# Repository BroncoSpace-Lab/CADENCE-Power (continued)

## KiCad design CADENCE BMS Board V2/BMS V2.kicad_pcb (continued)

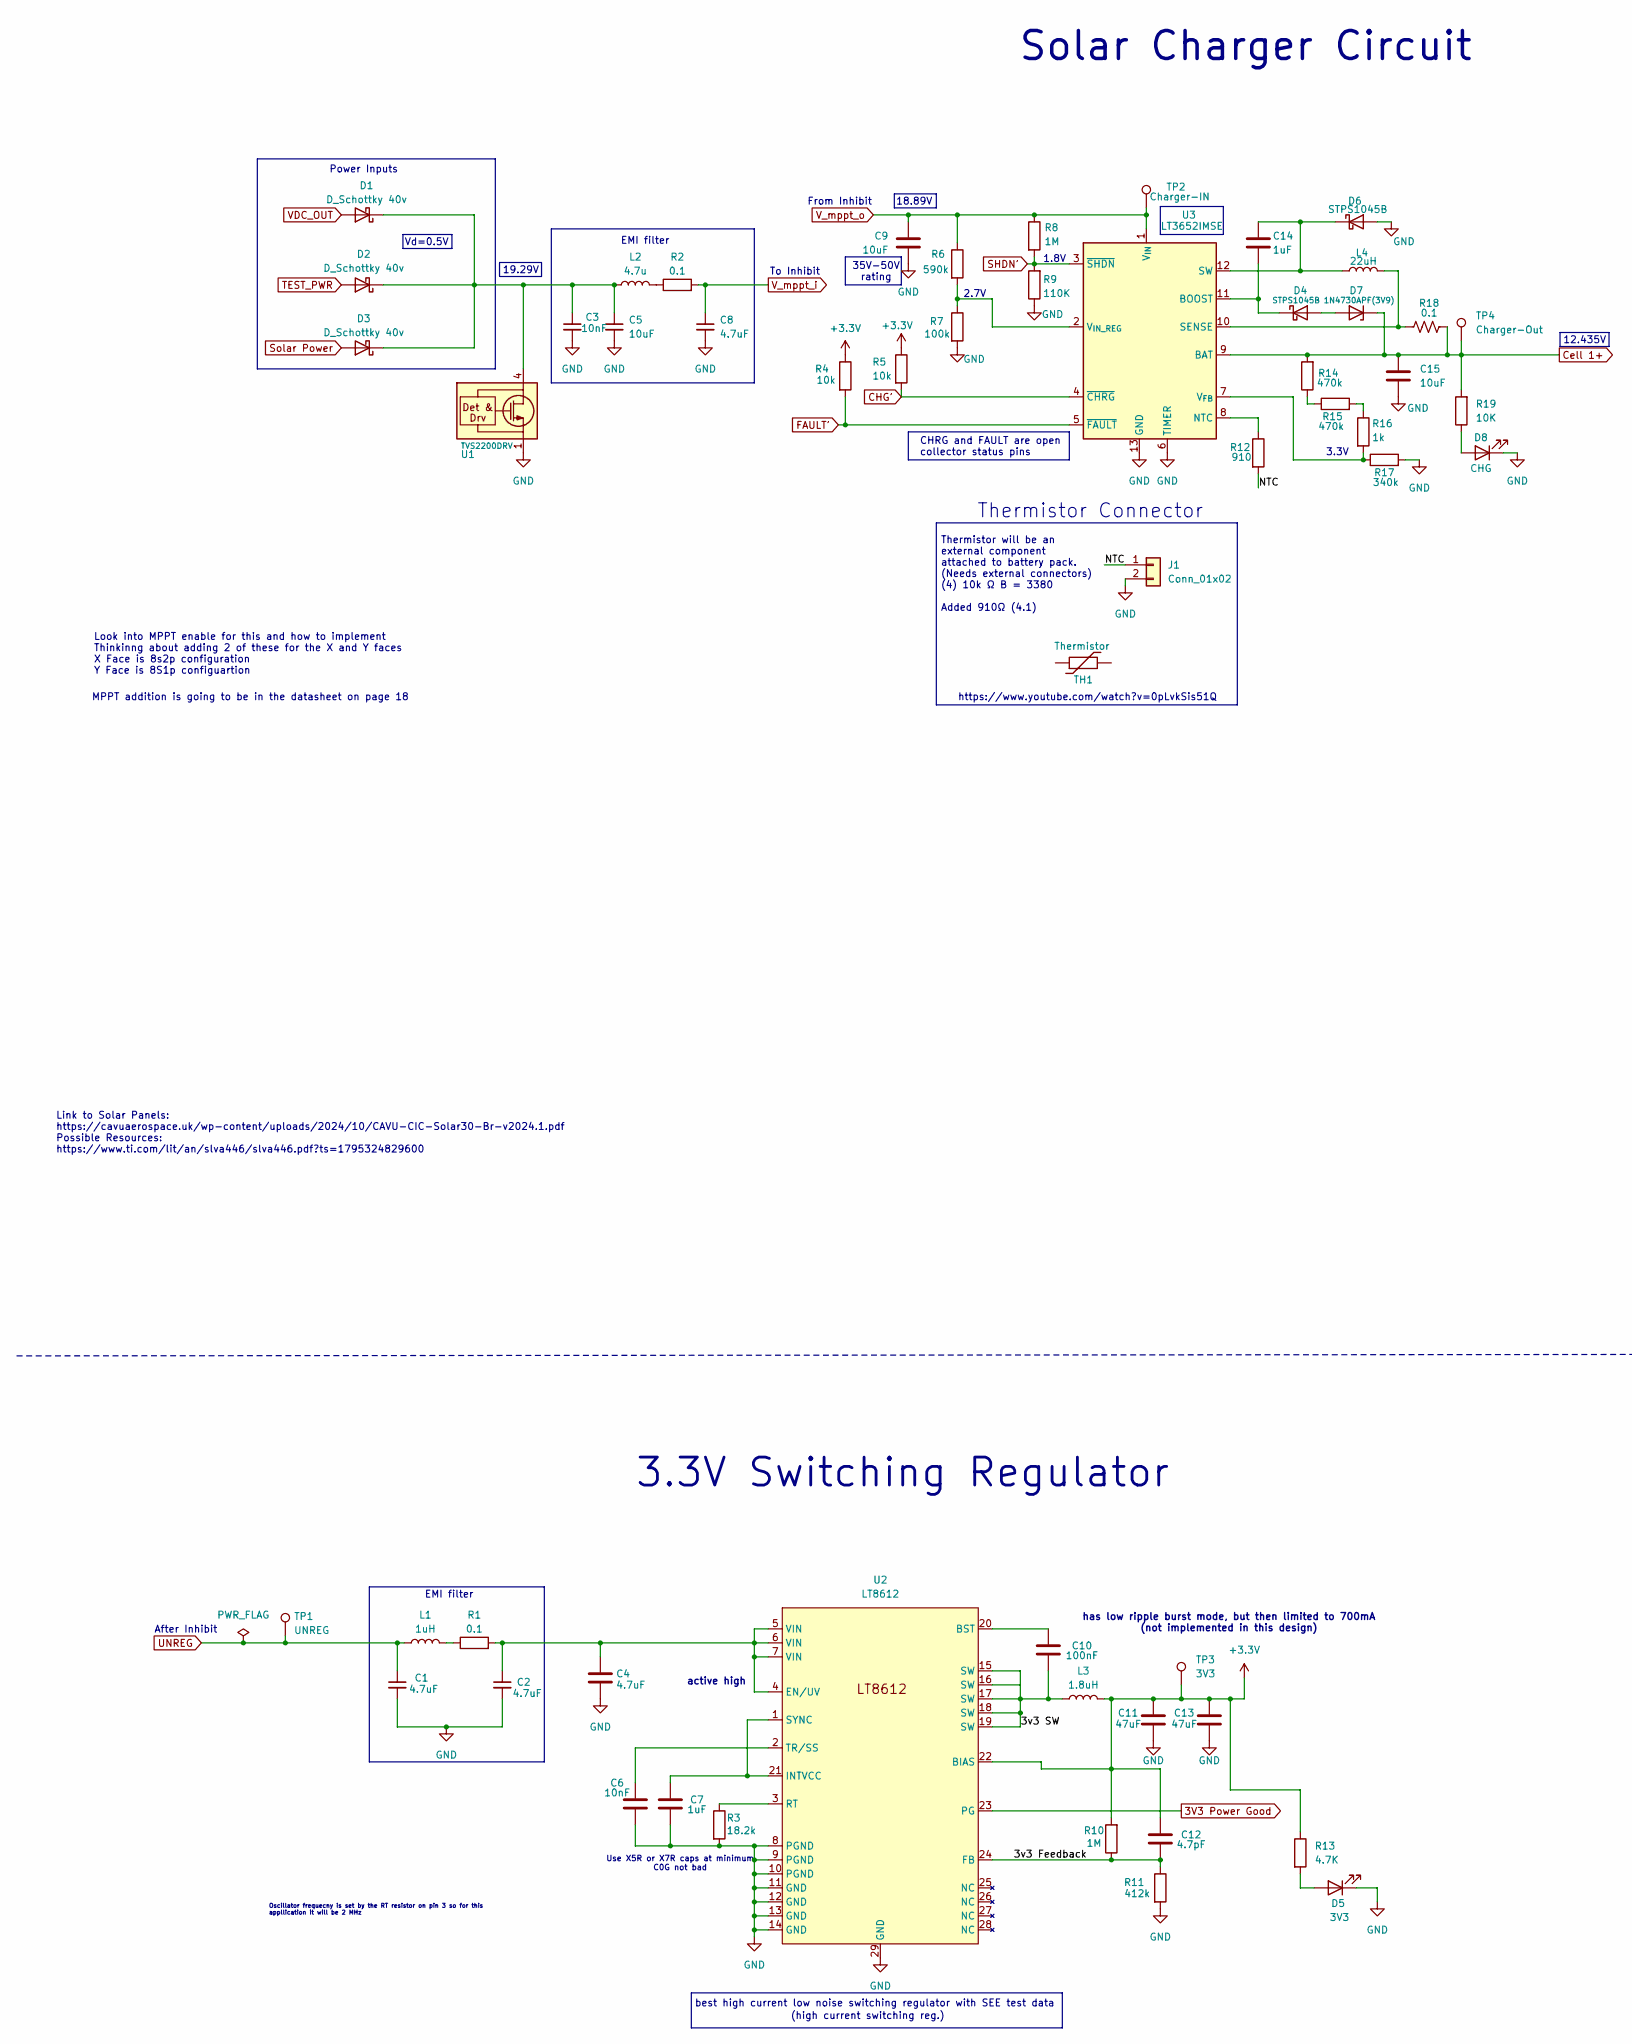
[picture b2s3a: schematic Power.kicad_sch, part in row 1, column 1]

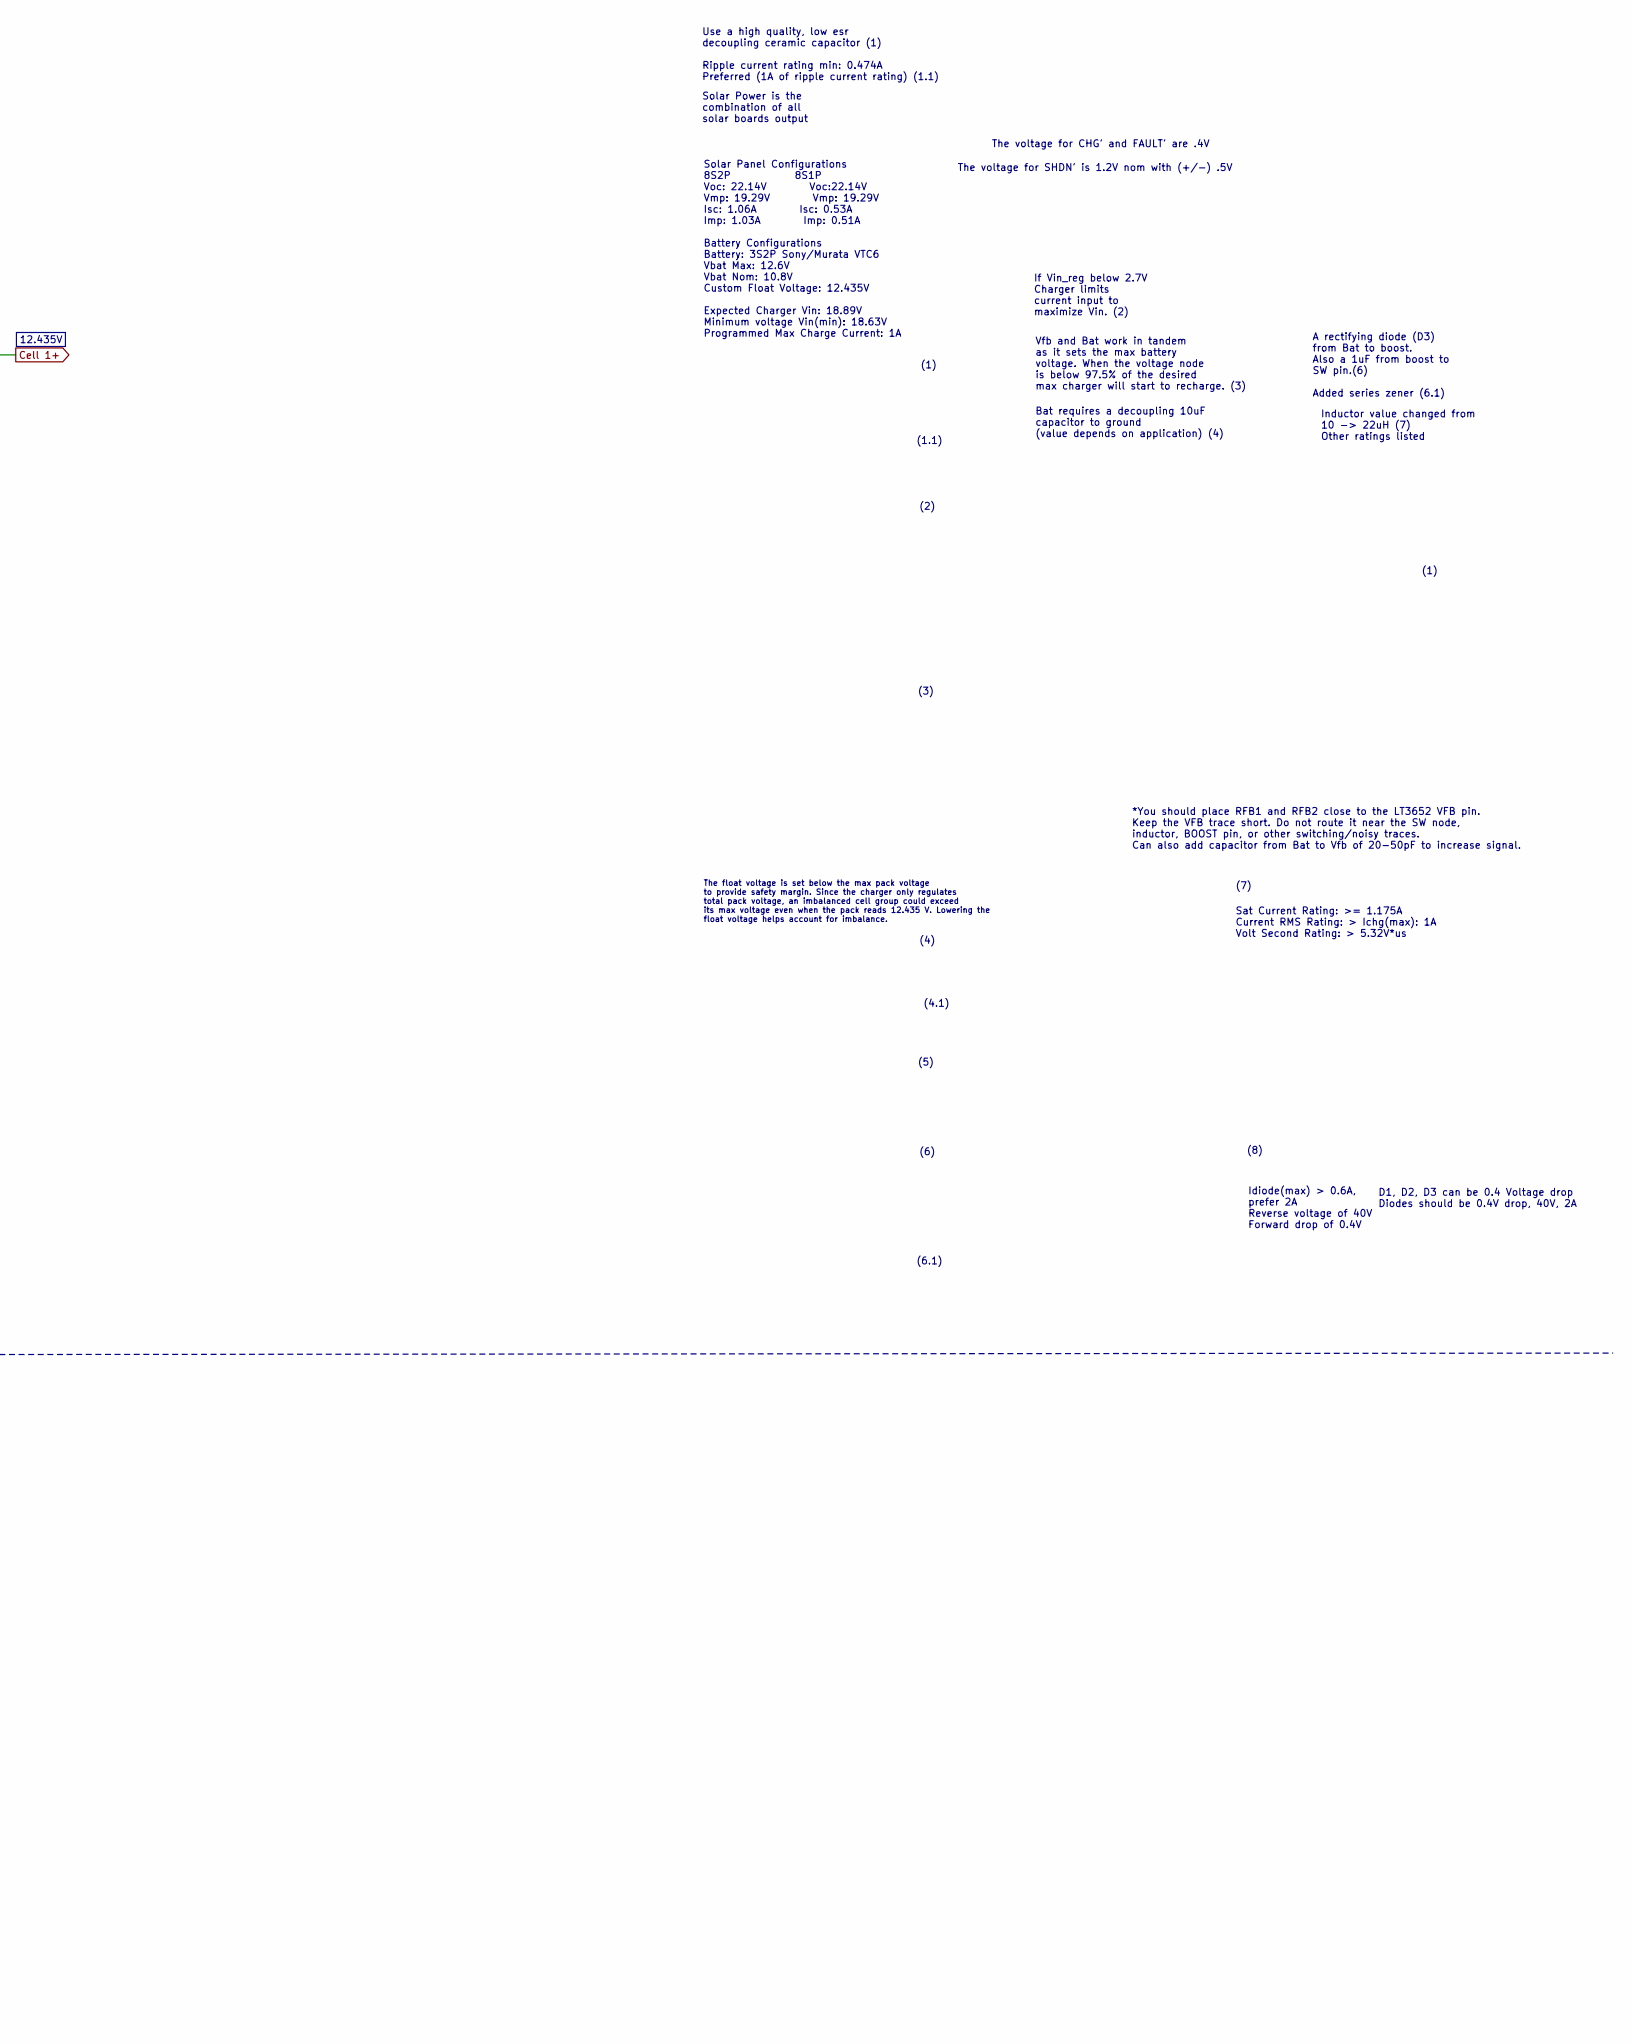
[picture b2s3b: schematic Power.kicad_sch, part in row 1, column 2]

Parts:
C1, C2, C4, C8: 4.7uF; C_1206_3216Metric
C3, C6: 10nF; C_0805_2012Metric
C5, C9, C15: 10uF; C_1210_3225Metric
C7, C14: 1uF; C_0805_2012Metric
C10: 100nF; C_0402_1005Metric
C11, C13: 47uF; C_2220_5750Metric
C12: 4.7pF; C_0603_1608Metric
D1, D2, D3: D_Schottky 40v; D_SMA
D4, D6: STPS1045B; DPAK_STM
D5: 3V3; LED_0402_1005Metric
D7: 1N4730APF(3V9); D_DO-41_SOD81_P12.70mm_Horizontal
D8: CHG; LED_0402_1005Metric
J1: Conn_01x02; JST_GH_SM02B-GHS-TB_1x02-1MP_P1.25mm_Horizontal
L1: 1uH; L_Taiyo-Yuden_NR-40xx
L2: 4.7u; FNR5040S4R7MT
L3: 1.8uH; L_Taiyo-Yuden_NR-40xx
L4: 22uH; L_10.4x10.4_H4.8
R1: 0.1; R_1206_3216Metric
R2, R18: 0.1; R_2512_6332Metric
R3: 18.2k; R_0603_1608Metric
R4, R5: 10k; R_1210_3225Metric
R6: 590k; R_0402_1005Metric_Pad0.72x0.64mm_HandSolder
R7: 100k; R_1206_3216Metric
R8: 1M
R9: 110K
R10: 1M; R_2512_6332Metric
R11: 412k; R_1206_3216Metric
R12: 910; R_0603_1608Metric
R13: 4.7K; R_1206_3216Metric
R14, R15: 470k; R_0603_1608Metric
R16: 1k; R_0603_1608Metric
R17: 340k; R_1206_3216Metric
R19: 10K; R_1210_3225Metric
TH1: Thermistor
TP1: UNREG; TestPoint_THTPad_D1.0mm_Drill0.5mm
TP2: Charger-IN; TestPoint_THTPad_D1.0mm_Drill0.5mm
TP3: 3V3; TestPoint_THTPad_D1.0mm_Drill0.5mm
TP4: Charger-Out; TestPoint_THTPad_D1.0mm_Drill0.5mm
U1: TVS2200DRV; WSON-6-1EP_2x2mm_P0.65mm_EP1x1.6mm
U2: LT8612; QFN50P300X600X80-29N-D
U3: LT3652IMSE; MSOP-12-1EP_3x4.039mm_P0.65mm_EP1.651x2.845mm

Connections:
3V3 Power Good: U2.23 (PG); also elsewhere on the board
+3.3V: C11.2, C12.2, C13.2, L3.2, R4.1, R5.1, R10.2, R13.1, TP3.1 (1_1), U2.22 (BIAS); also elsewhere on the board
/Power/3v3 Feedback: C12.1, R10.1, R11.1, U2.24 (FB)
/Power/3v3 SW: C10.1, L3.1, U2.15 (SW), U2.16 (SW), U2.17 (SW), U2.18 (SW), U2.19 (SW)
/Power/NTC: J1.1, R12.2
CHG': R5.2, U3.4 (~CHRG); also elsewhere on the board
Cell 1+: C15.1, D7.1 (K), R14.2, R18.2, R19.2, TP4.1 (1_1), U3.9 (BAT); also elsewhere on the board
FAULT': R4.2, U3.5 (~FAULT); also elsewhere on the board
unnamed: C3.1, C5.1, D1.1 (K), D2.1 (K), D3.1 (K), L2.1, U1.4 (IN), U1.5 (IN), U1.6 (IN)
unnamed: D4.1 (A), D7.2 (A)
unnamed: C14.2, D4.2 (K), U3.11 (BOOST)
unnamed: D5.2 (A), R13.2
unnamed: C14.1, D6.2 (K), L4.1, U3.12 (SW)
unnamed: D8.2 (A), R19.1
unnamed: L1.2, R1.1
unnamed: L2.2, R2.1
unnamed: R14.1, R15.1
unnamed: R15.2, R16.1
unnamed: C10.2, U2.20 (BST)
unnamed: C2.1, C4.1, R1.2, U2.4 (EN/UV), U2.5 (VIN), U2.6 (VIN), U2.7 (VIN)
unnamed: C7.2, U2.1 (SYNC), U2.21 (INTVCC)
unnamed: R3.1, U2.3 (RT)
unnamed: C6.2, U2.2 (TR/SS)
unnamed: R12.1, U3.8 (NTC)
unnamed: L4.2, R18.1, U3.10 (SENSE)
unnamed: R16.2, R17.1, U3.7 (V_{FB})
unnamed: R6.2, R7.1, U3.2 (V_{IN_REG})
SHDN': R8.2, R9.2, U3.3 (~SHDN); also elsewhere on the board
Solar1-: C1.2, C2.2, C3.2, C4.2, C5.2, C6.1, C7.1, C8.2, C9.2, C11.1, C13.1, C15.2, D5.1 (K), D6.1 (A), D8.1 (K), J1.2, R3.2, R7.2, R9.1, R11.2, R17.2, U1.1 (GND), U1.2 (GND), U1.3 (GND), U1.7 (GND), U2.8 (PGND), U2.9 (PGND), U2.10 (PGND), U2.11 (GND), U2.12 (GND), U2.13 (GND), U2.14 (GND), U2.29 (GND), U3.6 (TIMER), U3.13 (GND); also elsewhere on the board
Solar Power: D3.2 (A); also elsewhere on the board
TEST_PWR: D2.2 (A)
UNREG: C1.1, L1.1, TP1.1 (1_1); also elsewhere on the board
VDC_OUT: D1.2 (A); also elsewhere on the board
V_mppt_i: C8.1, R2.2; also elsewhere on the board
V_mppt_o: C9.1, R6.1, R8.1, TP2.1 (1_1), U3.1 (V_{IN}); also elsewhere on the board

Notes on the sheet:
Use X5R or X7R caps at minimum C0G not bad
(4.1)
MPPT addition is going to be in the datasheet on page 18
*You should place RFB1 and RFB2 close to the LT3652 VFB pin. Keep the VFB trace short. Do not route it near the SW node, inductor, BOOST pin, or other switching/noisy traces. Can also add capacitor from Bat to Vfb of 20-50pF to increase signal.
Link to Solar Panels: https://cavuaerospace.uk/wp-content/uploads/2024/10/CAVU-CIC-Solar30-Br-v2024.1.pdf Possible Resources: https://www.ti.com/lit/an/slva446/slva446.pdf?ts=1795324829600
Idiode(max) > 0.6A, prefer 2A Reverse voltage of 40V Forward drop of 0.4V
Inductor value changed from 10 -> 22uH (7) Other ratings listed
(3)
https://www.youtube.com/watch?v=0pLvkSis51Q
EMI filter
The voltage for SHDN' is 1.2V nom with (+/-) .5V
(6)
The float voltage is set below the max pack voltage to provide safety margin. Since the charger only regulates total pack voltage, an imbalanced cell group could exceed its max voltage even when the pack reads 12.435 V. Lowering the float voltage helps account for imbalance.
(8)
Oscillator frequecny is set by the RT resistor on pin 3 so for this appllication it will be 2 MHz
(1)
has low ripple burst mode, but then limited to 700mA (not implemented in this design)
best high current low noise switching regulator with SEE test data
From Inhibit
After Inhibit
If Vin_reg below 2.7V Charger limits current input to maximize Vin. (2)
D1, D2, D3 can be 0.4 Voltage drop Diodes should be 0.4V drop, 40V, 2A
(4)
Power Inputs
Solar Power is the combination of all solar boards output
1.8V
19.29V
Solar Panel Configurations 8S2P 8S1P Voc: 22.14V Voc:22.14V Vmp: 19.29V Vmp: 19.29V Isc: 1.06A Isc: 0.53A Imp: 1.03A Imp: 0.51A Battery Configurations Battery: 3S2P Sony/Murata VTC6 Vbat Max: 12.6V Vbat Nom: 10.8V Custom Float Voltage: 12.435V Expected Charger Vin: 18.89V Minimum voltage Vin(min): 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
3.3V Switching Regulator
The voltage for CHG' and FAULT' are .4V
To Inhibit
(5)
18.89V
Vd=0.5V
35V-50V rating
Sat Current Rating: >= 1.175A Current RMS Rating: > Ichg(max): 1A Volt Second Rating: > 5.32V*us
2.7V
CHRG and FAULT are open collector status pins
(1.1)
(2)

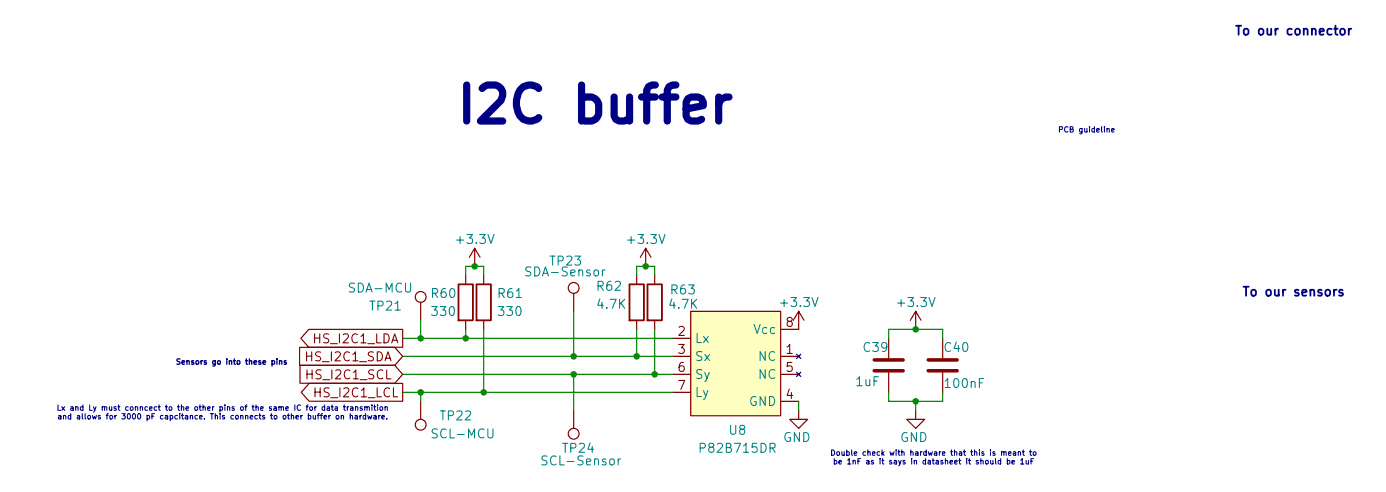
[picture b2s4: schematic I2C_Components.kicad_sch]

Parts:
C39: 1uF; R_0603_1608Metric
C40: 100nF; R_0603_1608Metric
R60, R61: 330; R_0805_2012Metric
R62, R63: 4.7K; R_0805_2012Metric
TP21: SDA-MCU; TestPoint_THTPad_D1.0mm_Drill0.5mm
TP22: SCL-MCU; TestPoint_THTPad_D1.0mm_Drill0.5mm
TP23: SDA-Sensor; TestPoint_THTPad_D1.0mm_Drill0.5mm
TP24: SCL-Sensor; TestPoint_THTPad_D1.0mm_Drill0.5mm
U8: P82B715DR; D8

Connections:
+3.3V: C39.1, C40.1, R60.1, R61.1, R62.1, R63.1, U8.8 (Vcc); also elsewhere on the board
HS_I2C1_LCL: R61.2, TP22.1 (1_1), U8.7 (Ly); also elsewhere on the board
HS_I2C1_LDA: R60.2, TP21.1 (1_1), U8.2 (Lx); also elsewhere on the board
HS_I2C1_SCL: R63.2, TP24.1 (1_1), U8.6 (Sy); also elsewhere on the board
HS_I2C1_SDA: R62.2, TP23.1 (1_1), U8.3 (Sx); also elsewhere on the board
Solar1-: C39.2, C40.2, U8.4 (GND); also elsewhere on the board

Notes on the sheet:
Sensors go into these pins
Lx and Ly must conncect to the other pins of the same IC for data transmition and allows for 3000 pF capcitance. This connects to other buffer on hardware.
I2C buffer
Double check with hardware that this is meant to be 1nF as it says in datasheet it should be 1uF
To our connector
To our sensors
PCB guideline

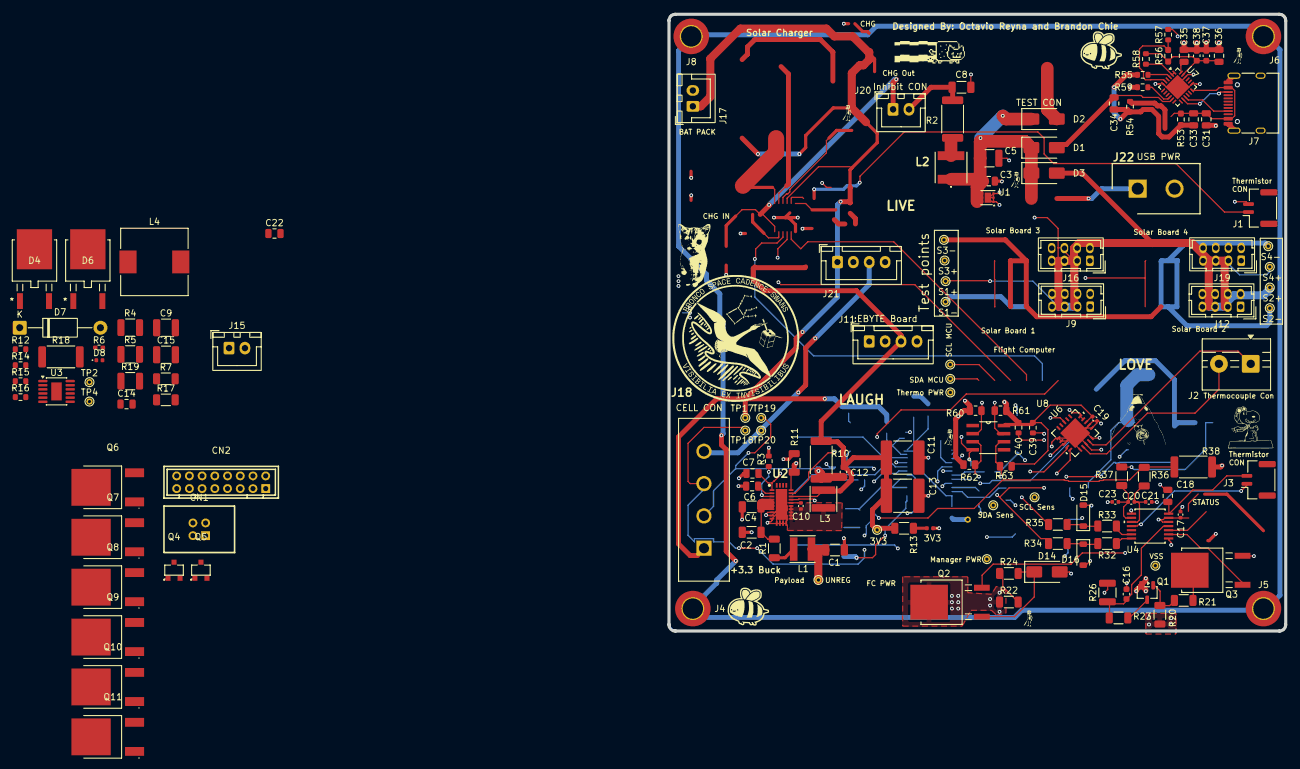
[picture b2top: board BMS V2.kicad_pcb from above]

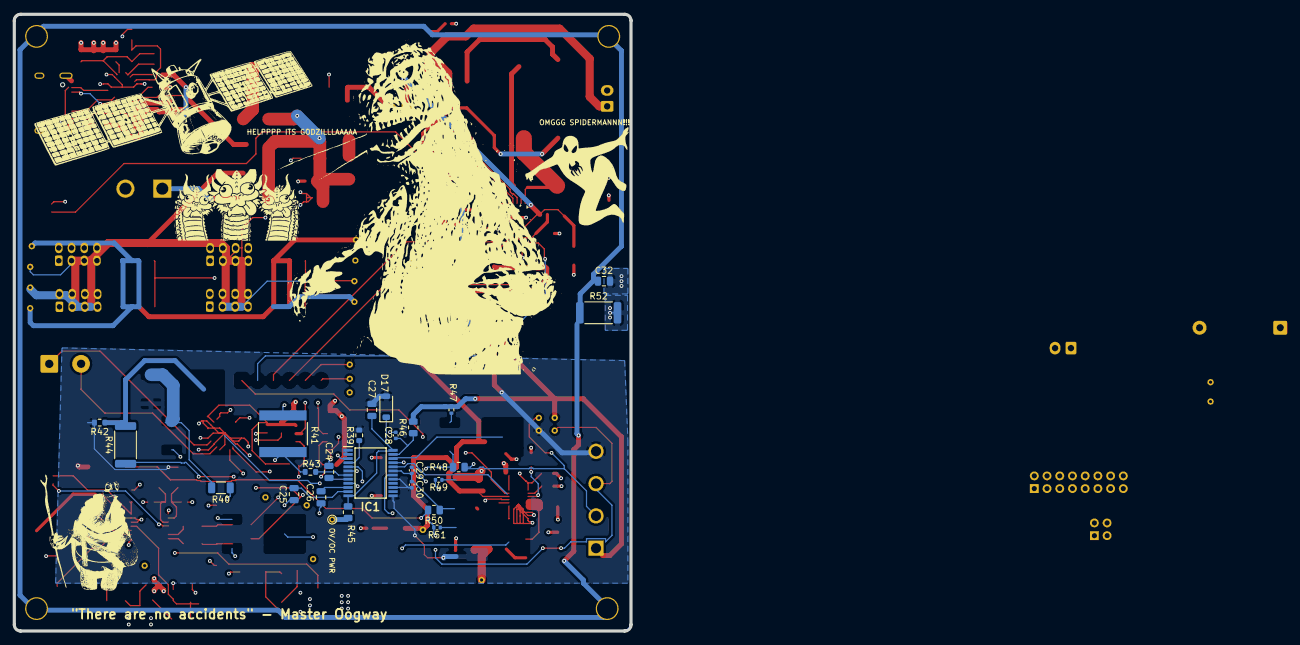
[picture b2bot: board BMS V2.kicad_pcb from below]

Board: 4 copper layers, 97.0 x 97.0 mm, 175 parts (25 on the bottom side), 93 nets.

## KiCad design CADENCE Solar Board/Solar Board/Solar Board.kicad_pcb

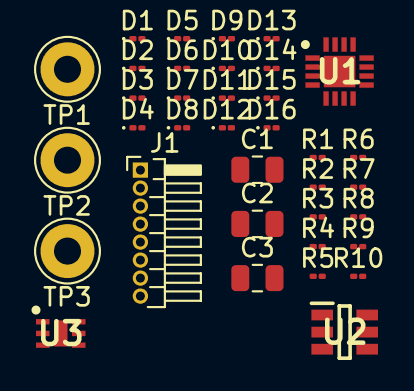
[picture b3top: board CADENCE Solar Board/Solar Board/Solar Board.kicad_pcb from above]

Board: 2 copper layers, 36 parts (0 on the bottom side), 32 nets, no tracks yet.

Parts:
C1, C3: 100nF; C_0805_2012Metric
C2: 10uF; C_0805_2012Metric
D1, D2, D3, D4, D5, D6, D7, D8, D9, D10, D11, D12, D13, D14, D15, D16: D; D_01005_0402Metric
J1: Conn_01x08; PinHeader_1x08_P1.00mm_Horizontal
R1, R2, R3, R5, R6, R7, R8, R10: 10k; R_01005_0402Metric
R4: 0.01; R_01005_0402Metric
R9: 1k; R_01005_0402Metric
TP1: Sensor Input; Pin_D1.3mm_L11.0mm_LooseFit
TP2: S1+; Pin_D1.3mm_L11.0mm_LooseFit
TP3: S1-; Pin_D1.3mm_L11.0mm_LooseFit
U1: INA230AIRGTT; QFN50P300X300X100-17N-D
U2: AD7414ARTZ-1REEL7; SOT95P280X145-6N
U3: OPT3001IDNPRQ1; SON65P200X200X65-7N-D

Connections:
+3.3V: C1.2, J1.1, R1.2, R4.1, R7.1, R8.2, R10.2, TP1.1 (1_1), U1.11 (BUS), U1.12 (IN-), U2.3 (VDD), U3.1 (VDD)
GND: C1.1, C2.2, C3.2, J1.4, U1.1 (A1), U1.2 (A0), U1.10 (GND), U2.2 (GND), U3.2 (ADDR), U3.3 (GND_1), U3.7 (GND_2)
HS_I2C1_LCL: J1.7, R3.2, R5.1, U3.4 (SCL)
HS_I2C1_LDA: J1.8, R2.1, R6.1, U3.6 (SDA)
unnamed: D1.2 (A), D2.2 (A)
unnamed: D1.1 (K), D4.2 (A)
unnamed: D2.1 (K), D3.2 (A)
unnamed: D3.1 (K), D6.2 (A)
unnamed: D4.1 (K), D8.2 (A)
unnamed: D5.2 (A), D6.1 (K)
unnamed: D7.2 (A), D8.1 (K)
unnamed: D5.1 (K), D10.2 (A)
unnamed: D9.2 (A), D10.1 (K)
unnamed: D11.2 (A), D12.1 (K)
unnamed: D11.1 (K), D16.2 (A)
unnamed: D7.1 (K), D12.2 (A)
unnamed: D13.2 (A), D14.1 (K)
unnamed: D13.1 (K), D15.1 (K)
unnamed: D9.1 (K), D14.2 (A)
unnamed: D15.2 (A), D16.1 (K)
unnamed: R1.1, U1.3 (ALERT)
unnamed: R4.2, U1.13 (IN+)
unnamed: R3.1, U1.5 (SCL)
unnamed: R2.2, U1.4 (SDA)
unnamed: R10.1, U1.9 (V_S+)
unnamed: C2.1, C3.1, R7.2, R9.2, U2.5 (ALERT)
unnamed: R9.1, U2.1 (AS)
unnamed: R5.2, U2.4 (SCL)
unnamed: R6.2, U2.6 (SDA)
unnamed: R8.1, U3.5 (INT)
Solar1+: J1.2, J1.3, TP2.1 (1_1)
Solar1-: J1.5, J1.6, TP3.1 (1_1)

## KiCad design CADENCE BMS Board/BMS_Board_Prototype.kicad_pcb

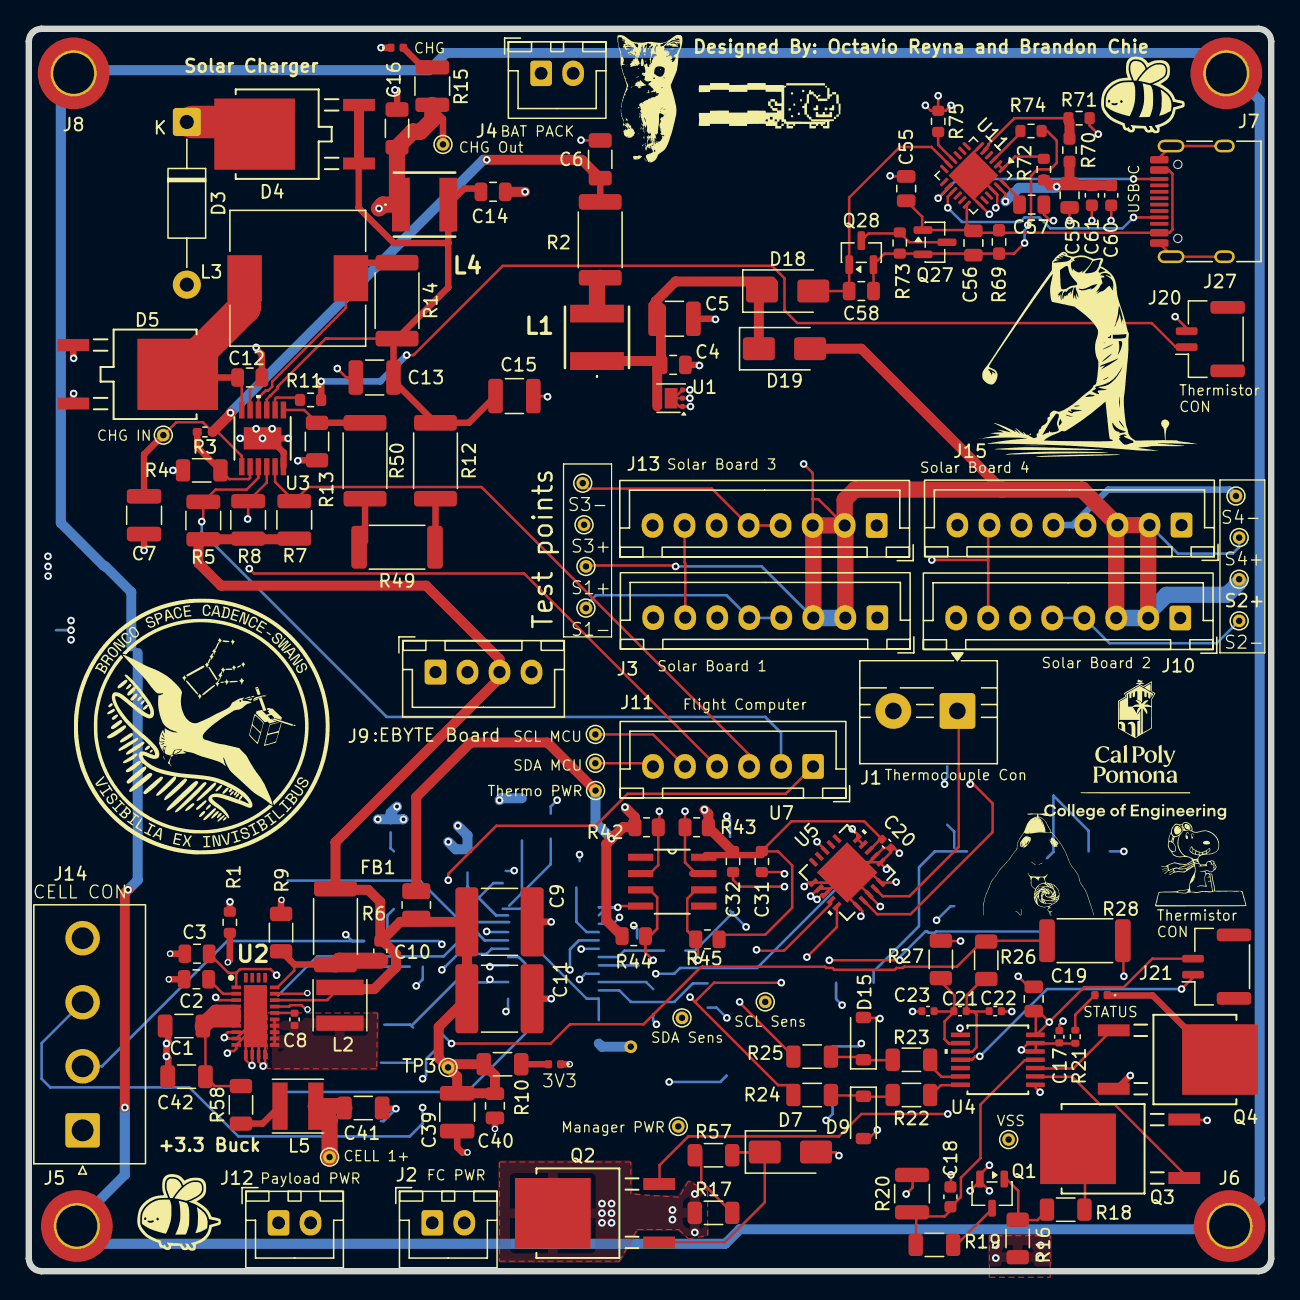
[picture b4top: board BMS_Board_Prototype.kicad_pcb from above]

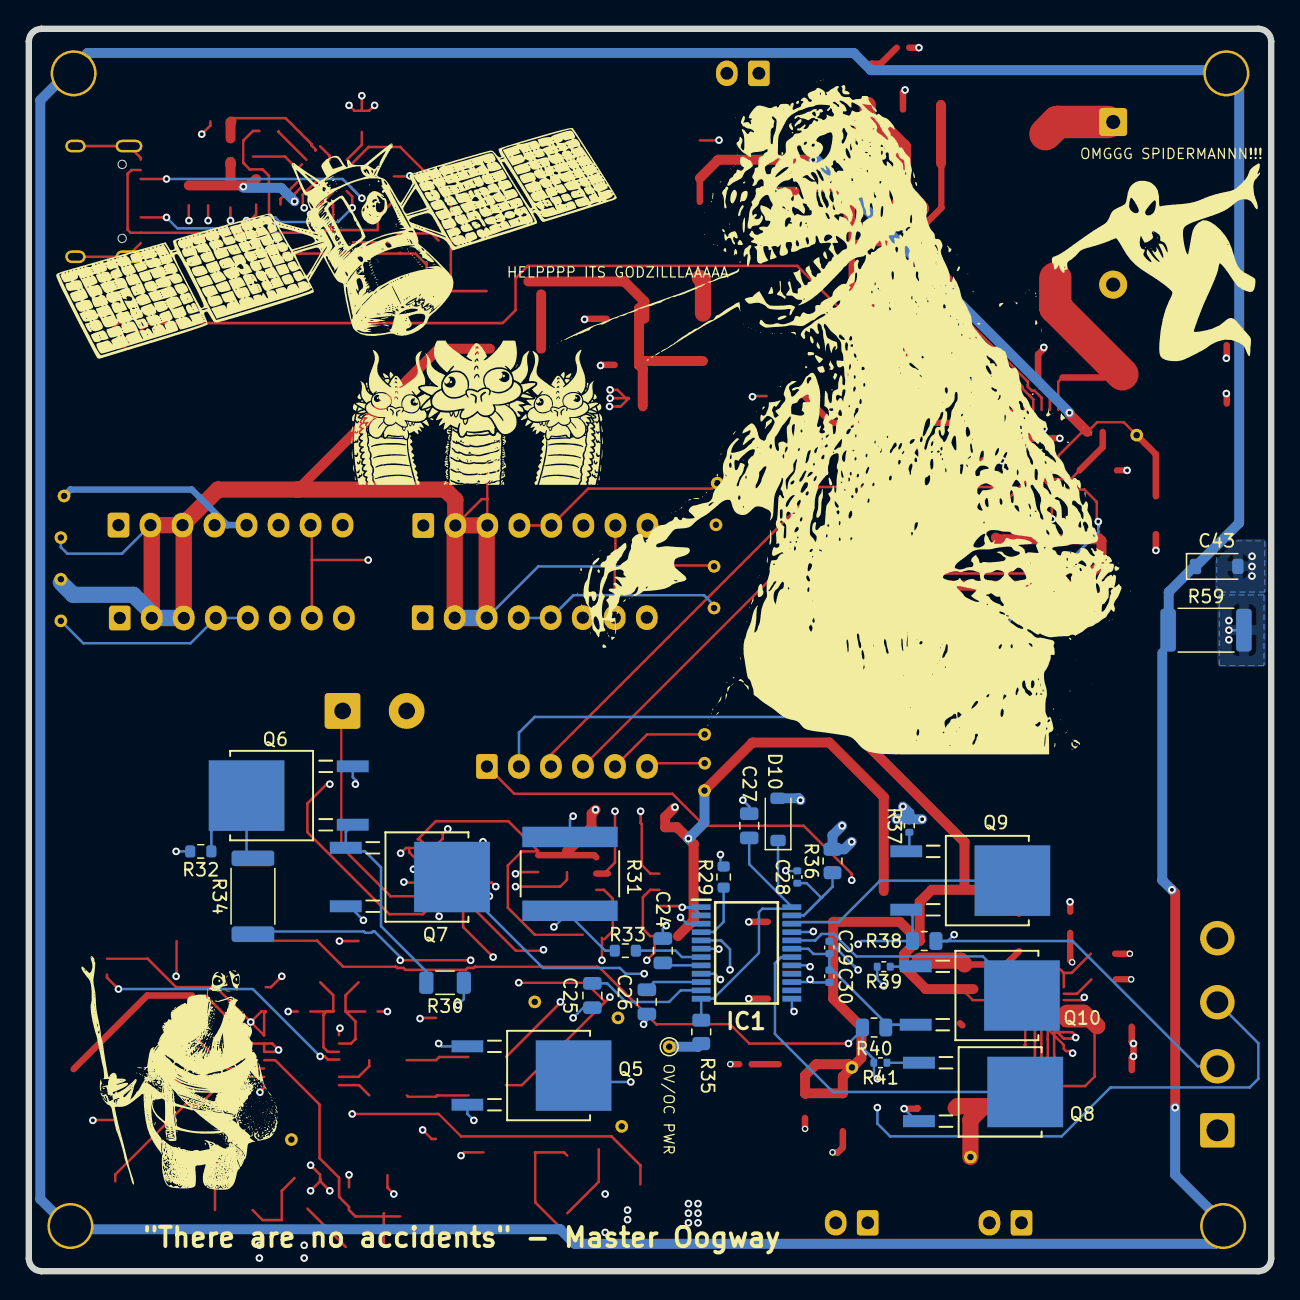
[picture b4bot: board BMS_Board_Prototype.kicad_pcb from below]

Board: 4 copper layers, 97.0 x 97.0 mm, 177 parts (31 on the bottom side), 95 nets.

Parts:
C1, C6, C16, C41, C42: 4.7uF; C_1206_3216Metric
C2, C4, C14, C40: 10nF; C_0805_2012Metric
C3, C12, C19, C27, C56, C57, C58, C59: 1uF; C_0805_2012Metric
C5, C7, C13, C15, C39: 10uF; C_1210_3225Metric
C8, C17, C20, C21, C22, C23, C28, C29, C30: 100nF; C_0402_1005Metric
C9, C11: 47uF; C_2220_5750Metric
C10: 4.7pF; C_0603_1608Metric
C18: 3300pF; C_0603_1608Metric
C24, C55: 3.3uF; C_0805_2012Metric
C25: 2200pF; C_0805_2012Metric
C26: .47uF; C_0805_2012Metric
C31: 1uF; R_0603_1608Metric
C32: 100nF; R_0603_1608Metric
C43: 1nF; D_SOD-123
C60, C61: 100nF; C_0603_1608Metric
D2: 3V3; LED_0402_1005Metric
D3: 1N4730APF-M (3V9); D_DO-41_SOD81_P12.70mm_Horizontal
D4, D5: STPS1045B-TR; DPAK_STM
D6: CHG; LED_0402_1005Metric
D7: 5V6; D_SMA
D8: LED; D_0402_1005Metric
D9, D15: 3.5V; D_SOD-123
D10: 15V; D_SOD-123
D18, D19: D_Schottky 40v; D_SMA
FB1: 600; L_1008_2520Metric
IC1: R5432V407BA; SOP65P760X140-24N
J1: Screw_Terminal_01x02; TerminalBlock_MaiXu_MX126-5.0-02P_1x02_P5.00mm
J2, J4, J12: Conn_01x02; JST_XH_B2B-XH-A_1x02_P2.50mm_Vertical
J3, J10, J13, J15: Conn_01x08; JST_XH_B8B-XH-A_1x08_P2.50mm_Vertical
J5, J6, J7, J8: Conn_01x01_Socket; MountingHole_3.2mm_M3_DIN965_Pad_TopOnly
J9: Conn_01x04; JST_XH_B4B-XH-A_1x04_P2.50mm_Vertical
J11: Conn_01x06; JST_XH_B6B-XH-A_1x06_P2.50mm_Vertical
J14: Conn_01x04; JST_NV_B04P-NV_1x04_P5.00mm_Vertical
J20, J21: Conn_01x02; JST_GH_SM02B-GHS-TB_1x02-1MP_P1.25mm_Horizontal
J27: USB_C_Receptacle_USB2.0_16P; USB_C_Receptacle_HRO_TYPE-C-31-M-12
L1, L4: 4.7u; FNR5040S4R7MT
L2: 1.8uH; L_Taiyo-Yuden_NR-40xx
L3: 22uH; L_10.4x10.4_H4.8
L5: 1uH; L_Taiyo-Yuden_NR-40xx
Q1: P-Channel FET; SOT-23-3
Q2, Q3, Q4: 60V Enhancement; SOT_N06-31-GE3_VIS
Q5, Q6, Q7: Q_NMOS_DSG; SOT_N06-31-GE3_VIS
Q8, Q9, Q10: N-MOS; SOT_N06-31-GE3_VIS
Q27, Q28: Q_PMOS_DGS; SOT-23
R1: 18.2k; R_0603_1608Metric
R2, R14: 0.1; R_2512_6332Metric
R3: 590k; R_0402_1005Metric_Pad0.72x0.64mm_HandSolder
R4, R16: 100k; R_1206_3216Metric
R5: 47k; R_1210_3225Metric
R6, R34, R59: 1M; R_2512_6332Metric
R7, R8: 10k; R_1210_3225Metric
R9: 412k; R_1206_3216Metric
R10: 4.7K; R_1206_3216Metric
R11: 910; R_0603_1608Metric
R12, R49: 470k; R_2512_6332Metric
R13: 340k; R_1206_3216Metric
R15: 10K; R_1210_3225Metric
R17, R57: 52.3k; R_1206_3216Metric
R18: 165k; R_1206_3216Metric
R19: 215K; R_1206_3216Metric
R20: 16.5k; R_1210_3225Metric
R21: 330; R_0402_1005Metric
R22, R23, R24, R25, R26, R27: 100; R_1206_3216Metric
R28: .037; R_2512_6332Metric
R29, R33, R75: 10K; R_0603_1608Metric
R30: 11.5K; R_1206_3216Metric
R31: .05; STA_CSSH2728_STP
R32: 2M; R_0603_1608Metric
R35, R36, R38, R40, R42, R43: 330; R_0805_2012Metric
R37, R39, R41: 100; R_0402_1005Metric
R44, R45: 4.7K; R_0805_2012Metric
R50: 1k; R_2512_6332Metric
R58: 0.1; R_1206_3216Metric
R69: 10K; R_0603_1608Metric_Pad0.98x0.95mm_HandSolder
R70: 5.1K; R_0603_1608Metric_Pad0.98x0.95mm_HandSolder
R71: 2.4K; R_0603_1608Metric
R72: 0; R_0603_1608Metric
R73, R74: 49.9K; R_0603_1608Metric
TP1: UNREG; TestPoint_THTPad_D1.0mm_Drill0.5mm
TP2: Charger-IN; TestPoint_THTPad_D1.0mm_Drill0.5mm
TP3: 3V3; TestPoint_THTPad_D1.0mm_Drill0.5mm
TP4: Charger-Out; TestPoint_THTPad_D1.0mm_Drill0.5mm
TP5: Manager-PWR; TestPoint_THTPad_D1.0mm_Drill0.5mm
TP6: VSS; TestPoint_THTPad_D1.0mm_Drill0.5mm
TP7: Thermo-PWR; TestPoint_THTPad_D1.0mm_Drill0.5mm
TP8: OV/OC PWR; TestPoint_THTPad_D1.0mm_Drill0.5mm
TP9: S1-; TestPoint_THTPad_D1.0mm_Drill0.5mm
TP10: S1+; TestPoint_THTPad_D1.0mm_Drill0.5mm
TP11: S2+; TestPoint_THTPad_D1.0mm_Drill0.5mm
TP12: S2-; TestPoint_THTPad_D1.0mm_Drill0.5mm
TP13: S3+; TestPoint_THTPad_D1.0mm_Drill0.5mm
TP14: S3-; TestPoint_THTPad_D1.0mm_Drill0.5mm
TP15: S4+; TestPoint_THTPad_D1.0mm_Drill0.5mm
TP16: S4-; TestPoint_THTPad_D1.0mm_Drill0.5mm
TP17: SDA-MCU; TestPoint_THTPad_D1.0mm_Drill0.5mm
TP18: SCL-MCU; TestPoint_THTPad_D1.0mm_Drill0.5mm
TP19: SDA-Sensor; TestPoint_THTPad_D1.0mm_Drill0.5mm
TP20: SCL-Sensor; TestPoint_THTPad_D1.0mm_Drill0.5mm
U1: TVS2200DRV; WSON-6-1EP_2x2mm_P0.65mm_EP1x1.6mm
U2: LT8612; QFN50P300X600X80-29N-D
U3: LT3652IMSE#PBF; MSOP-12_MSE_LIT
U4: BQ34Z100-R2; PW14_TEX
U5: MCP9600-E_MX; MQFN20_NU_MCH
U7: P82B715DR; D8
U11: CYPD3177-24LQ; QFN-24-1EP_4x4mm_P0.5mm_EP2.75x2.75mm

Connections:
3V3 Power Good: J11.1, U2.23 (PG)
+3.3V: C9.2, C10.2, C11.2, C39.1, C40.1, FB1.2, J3.1, J9.3, J10.1, J13.1, J15.1, L2.2, R5.1, R6.2, R7.1, R8.1, R10.1, R75.1, TP3.1 (1_1), U2.22 (BIAS)
+3.3V Q: C20.2, C31.1, C32.1, FB1.1, R42.1, R43.1, R44.1, R45.1, TP7.1 (1_1), U5.8 (VDD), U7.8 (Vcc)
/Power/3v3 Feedback: C10.1, R6.1, R9.1, U2.24 (FB)
/Power/3v3 SW: C8.1, L2.1, U2.15 (SW), U2.16 (SW), U2.17 (SW), U2.18 (SW), U2.19 (SW)
/Sensors/REGIN: C17.1, Q2.2 (S), R21.1, U4.5 (CE), U4.6 (REGIN)
/Sensors/Serial Clock: R23.1, U4.13 (P4/SCL)
/Sensors/Serial Data: R22.1, U4.14 (P3/SDA)
/Sensors/Voltage Divider: C18.2, R19.2, R20.1, U4.4 (BAT)
/Sensors/Voltage Divider Enable: Q3.3 (D), R18.2
CB1: IC1.22 (CB1), Q9.3 (G)
CB2: IC1.20 (CB2), Q10.3 (G)
CB3: IC1.18 (CB3), Q8.3 (G)
CC1: J27.A5 (CC1), U11.15 (CC1)
CC2: J27.B5 (CC2), U11.14 (CC2)
CHG': J11.4, R8.2, U3.4 (~CHRG)
Cell 1+: C16.1, C41.1, J2.1, J4.1, J9.1, J12.1, J14.1, L4.1, L5.1, Q1.2 (S), Q2.3 (D), R15.1, R16.1, R17.1, R35.1, R36.2, R37.2, TP1.1 (1_1), TP4.1 (1_1), TP5.1 (1_1), TP8.1 (1_1)
Cell 2+: J14.2, R38.2, R39.2
Cell 3+: J14.3, R26.2, R28.1, R40.2, R41.2
Cell 3-: C1.2, C2.1, C3.1, C4.2, C5.2, C6.2, C7.2, C9.1, C11.1, C13.2, C14.2, C15.2, C16.2, C17.2, C18.1, C19.1, C20.1, C22.1, C23.1, C24.1, C25.2, C26.1, C27.2, C30.2, C31.2, C32.2, C39.2, C40.2, C41.2, C42.2, C43.2, C55.2, C57.1, C59.2, C60.2, C61.2, D2.1 (K), D5.1 (A), D6.1 (K), D7.2 (A), D9.2 (A), D10.2 (A), D15.2 (A), IC1.1 (CTLC), IC1.2 (CTLD), IC1.9 (VSS), IC1.13 (SEL2), IC1.15 (VC5), IC1.17 (VC4), J2.2, J3.4, J3.5, J3.6, J4.2, J9.2, J9.4, J10.4, J10.5, J10.6, J12.2, J13.4, J13.5, J13.6, J14.4, J15.4, J15.5, J15.6, J20.2, J27.A1 (GND), J27.A12 (GND), J27.B1 (GND), J27.B12 (GND), J27.SH (SHIELD), Q3.2 (S), Q4.2 (S), Q5.2 (S), Q6.2 (S), Q8.2 (S), R1.2, R4.2, R9.2, R13.2, R20.2, R27.2, R28.2, R29.2, R31.1, R32.2, R59.2, R71.2, TP6.1 (1_1), TP9.1 (1_1), TP12.1 (1_1), TP14.1 (1_1), TP16.1 (1_1), U1.1 (GND), U1.2 (GND), U1.3 (GND), U1.7 (GND), U2.8 (PGND), U2.9 (PGND), U2.10 (PGND), U2.11 (GND), U2.12 (GND), U2.13 (GND), U2.14 (GND), U2.29 (GND), U3.6 (TIMER), U3.13 (GND), U4.1 (P2), U4.8 (VSS), U5.1 (GND), U5.3 (GND), U5.5 (GND), U5.6 (GND), U5.7 (GND), U5.9 (GND), U5.10 (GND), U5.13 (GND), U5.16 (ADDR), U5.17 (GND), U5.18 (GND), U5.21 (EXP), U7.4 (GND), U11.6 (ISNK_FINE), U11.19 (GND), U11.22 (GND), U11.25 (GND)
DRAIN: IC1.5 (DRAIN), Q5.3 (G)
FAULT': J11.3, R7.2, U3.5 (~FAULT)
HS_I2C1_LCL: J3.7, J10.7, J11.5, J13.7, J15.7, R43.2, TP18.1 (1_1), U7.7 (Ly)
HS_I2C1_LDA: J3.8, J10.8, J11.6, J13.8, J15.8, R42.2, TP17.1 (1_1), U7.2 (Lx)
HS_I2C1_SCL: R25.2, R45.2, TP20.1 (1_1), U5.19 (SCL), U7.6 (Sy)
HS_I2C1_SDA: R24.2, R44.2, TP19.1 (1_1), U5.20 (SDA), U7.3 (Sx)
NTC: J20.1, R11.2
unnamed: C43.1, J5.1 (1_1), J6.1 (1_1), J7.1 (1_1), J8.1 (1_1), R59.1
unnamed: D2.2 (A), R10.2
unnamed: C12.2, D3.2 (A), U3.11 (BOOST)
unnamed: D3.1 (K), D4.2 (K)
unnamed: C13.1, C14.1, C15.1, D4.1 (A), L4.2, R12.1, R14.2, U3.9 (BAT)
unnamed: C12.1, D5.2 (K), L3.1, U3.12 (SW)
unnamed: D6.2 (A), R15.2
unnamed: D7.1 (K), Q2.1 (G), R57.2
unnamed: D8.2 (A), R21.2
unnamed: D8.1 (K), Q4.3 (D)
unnamed: D9.1 (K), R22.2, R24.1
unnamed: D15.1 (K), R23.2, R25.1
unnamed: C4.1, C5.1, D18.1 (K), D19.1 (K), L1.1, U1.4 (IN), U1.5 (IN), U1.6 (IN)
unnamed: IC1.3 (COUT), R34.1
unnamed: C26.2, IC1.10 (CT1)
unnamed: C25.1, IC1.11 (CT2)
unnamed: C24.2, IC1.8 (CTLT)
unnamed: IC1.6 (DOUT), Q7.3 (G)
unnamed: IC1.7 (SENS), R33.2
unnamed: C28.1, IC1.23 (VC1), R36.1
unnamed: C28.2, C29.1, IC1.21 (VC2), Q9.2 (S), R38.1
unnamed: C29.2, C30.1, IC1.19 (VC3), Q10.2 (S), R40.1
unnamed: J1.1, U5.4 (VIN-)
unnamed: J1.2, U5.2 (VIN+)
unnamed: J21.1, U4.11 (P6/TS)
unnamed: L1.2, R2.1
unnamed: L5.2, R58.1
unnamed: Q1.3 (D), R19.1
unnamed: Q1.1 (G), R16.2, R18.1
unnamed: Q3.1 (G), U4.2 (VEN)
unnamed: Q4.1 (G), U4.3 (P1)
unnamed: Q5.1 (D), R30.1
unnamed: Q6.1 (D), Q7.1 (D), R30.2
unnamed: Q6.3 (G), R32.1, R34.2
unnamed: Q7.2 (S), R31.2, R33.1
unnamed: Q8.1 (D), R41.1
unnamed: Q9.1 (D), R37.1
unnamed: Q10.1 (D), R39.1
unnamed: C56.2, C58.2, Q27.2 (G), Q28.2 (G), R69.2, R73.2, R74.1
unnamed: Q27.3 (S), Q28.3 (S), R73.1
unnamed: R12.2, R49.1
unnamed: R17.2, R57.1
unnamed: R49.2, R50.1
unnamed: C8.2, U2.20 (BST)
unnamed: C1.1, C42.1, R58.2, U2.4 (EN/UV), U2.5 (VIN), U2.6 (VIN), U2.7 (VIN)
unnamed: C3.2, U2.1 (SYNC), U2.21 (INTVCC)
unnamed: R1.1, U2.3 (RT)
unnamed: C2.2, U2.2 (TR/SS)
unnamed: R11.1, U3.8 (NTC)
unnamed: L3.2, R14.1, U3.10 (SENSE)
unnamed: R13.1, R50.2, U3.7 (VFB)
unnamed: C6.1, C7.1, R2.2, R3.1, TP2.1 (1_1), U3.1 (VIN)
unnamed: R3.2, R4.1, U3.2 (VIN_REG)
unnamed: C21.1, C22.2, R26.1, U4.10 (SRN)
unnamed: C21.2, C23.2, R27.1, U4.9 (SRP)
unnamed: R75.2, U11.10 (FLIP)
unnamed: R70.2, R71.1, U11.5 (ISNK_COARSE)
unnamed: R72.2, U11.1 (VBUS_MIN), U11.2 (VBUS_MAX)
unnamed: C57.2, U11.24 (VCCD)
REG25: C19.2, J21.2, U4.7 (REG25)
SHDN': J11.2, R5.2, U3.3 (~SHDN)
Solar Power: D19.2 (A), J3.2, J3.3, J10.2, J10.3, J13.2, J13.3, J15.2, J15.3, TP10.1 (1_1), TP11.1 (1_1), TP13.1 (1_1), TP15.1 (1_1)
VBUS: C55.1, C56.1, J27.A4 (VBUS), J27.A9 (VBUS), J27.B4 (VBUS), J27.B9 (VBUS), Q27.1 (D), R69.1, U11.18 (VBUS_IN)
VBUS_EN: R74.2, U11.3 (VBUS_FET_EN)
VDC_OUT: C58.1, D18.2 (A), Q28.1 (D), U11.11 (VDC_OUT)
VDD: C27.1, D10.1 (K), IC1.12 (SEL1), IC1.24 (VDD), R35.2
VDDD: C59.1, C60.1, C61.1, R70.1, R72.1, U11.23 (VDDD)
VMP: IC1.4 (VMP), R29.1
